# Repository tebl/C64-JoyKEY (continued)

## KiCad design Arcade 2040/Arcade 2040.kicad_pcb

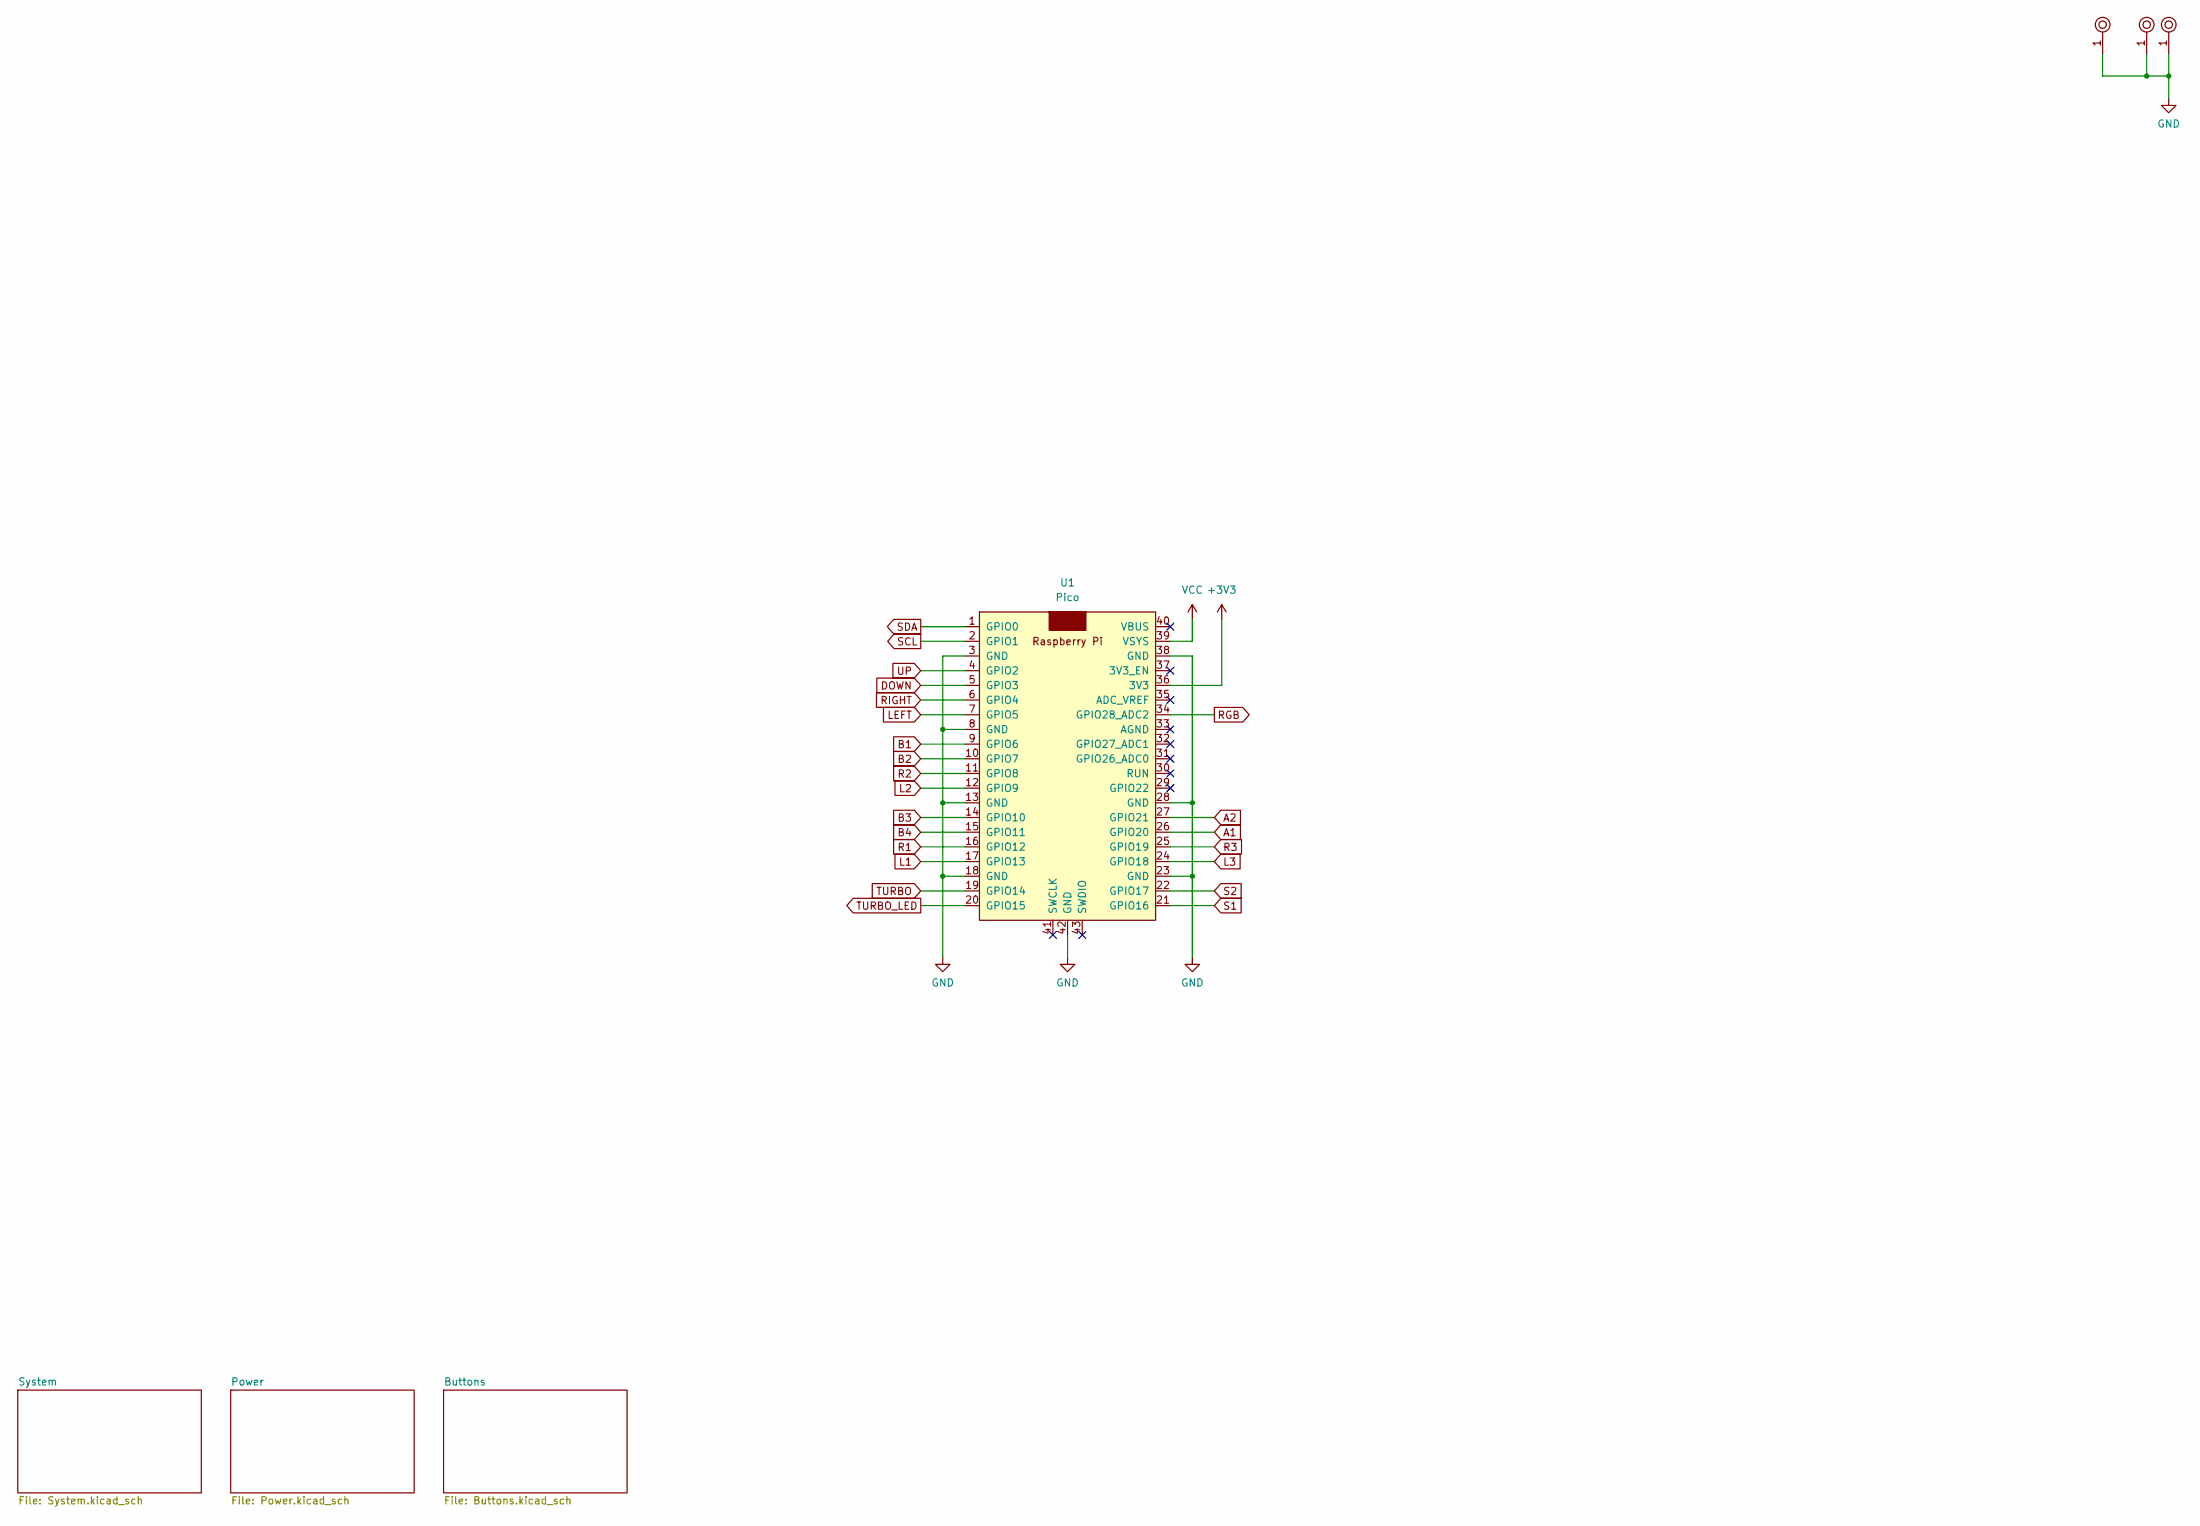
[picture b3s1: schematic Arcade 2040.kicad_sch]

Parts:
M1, M3, M4: Mounting; M3_pin
U1: Pico; RPi_Pico_SMD_TH_Clean

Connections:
+3V3: U1.36 (3V3); also elsewhere on the board
A1: U1.26 (GPIO20); also elsewhere on the board
A2: U1.27 (GPIO21); also elsewhere on the board
B1: U1.9 (GPIO6); also elsewhere on the board
B2: U1.10 (GPIO7); also elsewhere on the board
B3: U1.14 (GPIO10); also elsewhere on the board
B4: U1.15 (GPIO11); also elsewhere on the board
DOWN: U1.5 (GPIO3); also elsewhere on the board
GND: M1.1, M3.1, M4.1, U1.3 (GND), U1.8 (GND), U1.13 (GND), U1.18 (GND), U1.23 (GND), U1.28 (GND), U1.38 (GND), U1.42 (GND); also elsewhere on the board
L1: U1.17 (GPIO13); also elsewhere on the board
L2: U1.12 (GPIO9); also elsewhere on the board
L3: U1.24 (GPIO18); also elsewhere on the board
LEFT: U1.7 (GPIO5); also elsewhere on the board
R1: U1.16 (GPIO12); also elsewhere on the board
R2: U1.11 (GPIO8); also elsewhere on the board
R3: U1.25 (GPIO19); also elsewhere on the board
RGB: U1.34 (GPIO28_ADC2); also elsewhere on the board
RIGHT: U1.6 (GPIO4); also elsewhere on the board
S1: U1.21 (GPIO16); also elsewhere on the board
S2: U1.22 (GPIO17); also elsewhere on the board
SCL: U1.2 (GPIO1); also elsewhere on the board
SDA: U1.1 (GPIO0); also elsewhere on the board
TURBO: U1.19 (GPIO14); also elsewhere on the board
TURBO_LED: U1.20 (GPIO15); also elsewhere on the board
UP: U1.4 (GPIO2); also elsewhere on the board
VCC: U1.39 (VSYS); also elsewhere on the board

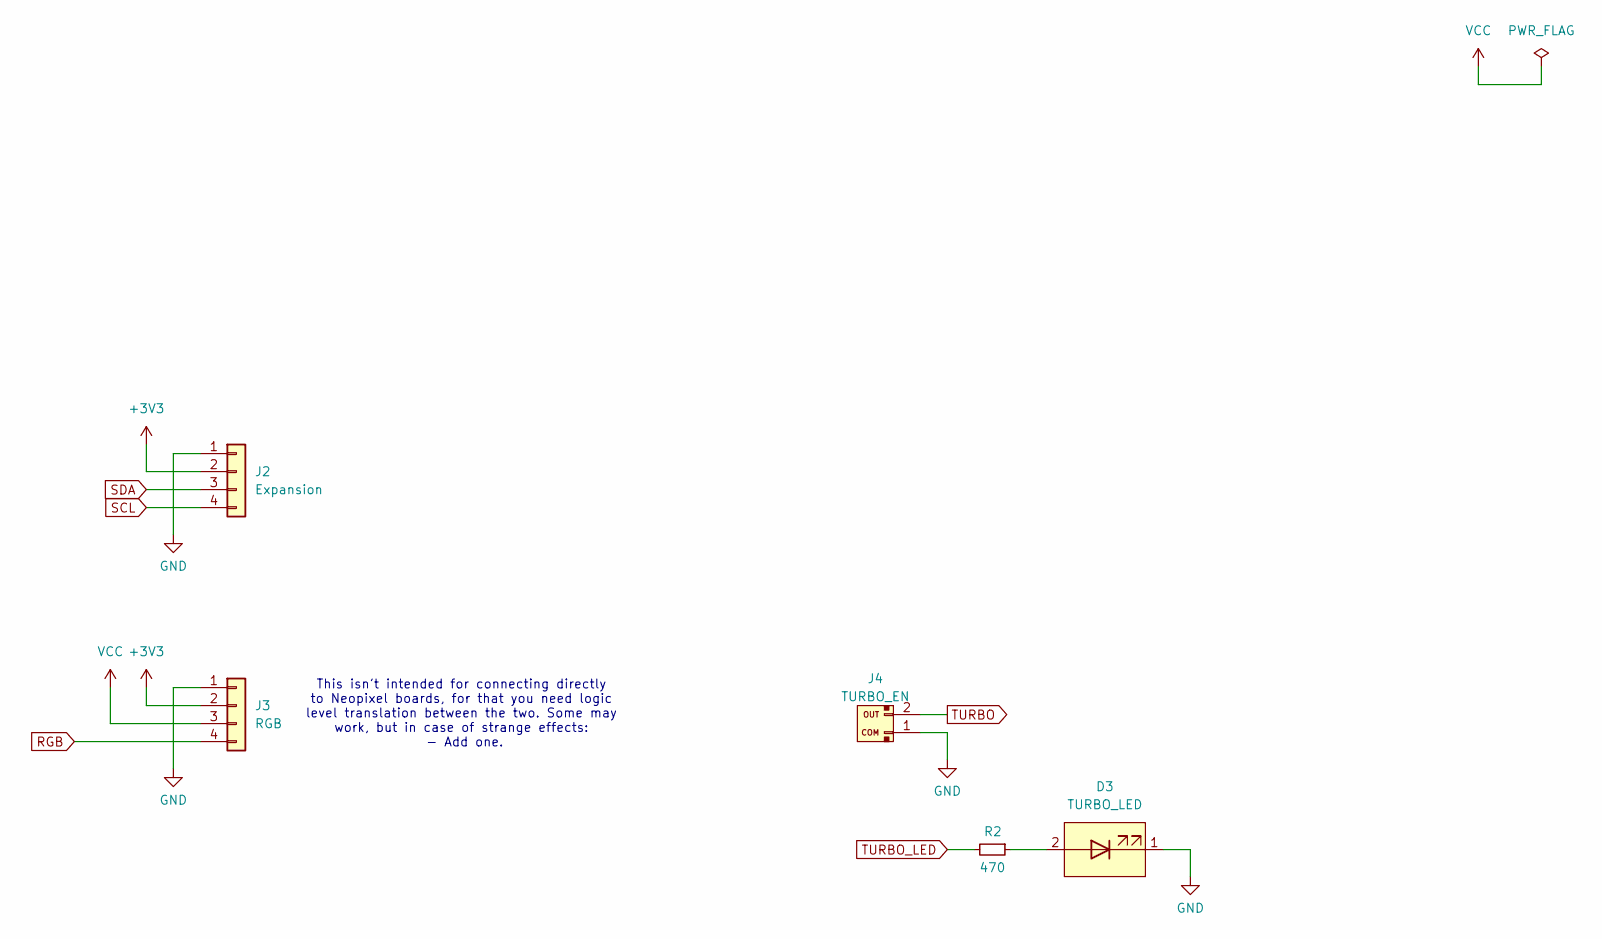
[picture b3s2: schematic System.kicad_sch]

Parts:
D3: TURBO_LED; JST_XH_B2B-XH-A_1x02_P2.50mm_Vertical
J2: Expansion; JST_XH_B4B-XH-A_1x04_P2.50mm_Vertical
J3: RGB; JST_XH_B4B-XH-A_1x04_P2.50mm_Vertical
J4: TURBO_EN; JST_XH_B2B-XH-A_1x02_P2.50mm_Vertical
R2: 470; R_Axial_DIN0207_L6.3mm_D2.5mm_P10.16mm_Horizontal

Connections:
+3V3: J2.2, J3.2; also elsewhere on the board
GND: D3.1 (K), J2.1, J3.1, J4.1; also elsewhere on the board
unnamed: D3.2 (A), R2.1
RGB: J3.4; also elsewhere on the board
SCL: J2.4; also elsewhere on the board
SDA: J2.3; also elsewhere on the board
TURBO: J4.2; also elsewhere on the board
TURBO_LED: R2.2; also elsewhere on the board
VCC: J3.3; also elsewhere on the board

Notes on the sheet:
This isn't intended for connecting directly to Neopixel boards, for that you need logic level translation between the two. Some may work, but in case of strange effects: - Add one.

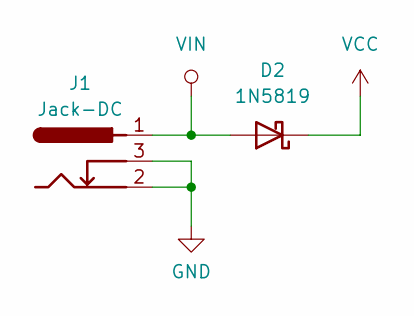
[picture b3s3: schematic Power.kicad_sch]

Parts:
D2: 1N5819; D_DO-41_SOD81_P10.16mm_Horizontal
J1: Jack-DC; BARREL_JACK

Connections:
GND: J1.2, J1.3; also elsewhere on the board
VCC: D2.1 (K); also elsewhere on the board
VIN: D2.2 (A), J1.1

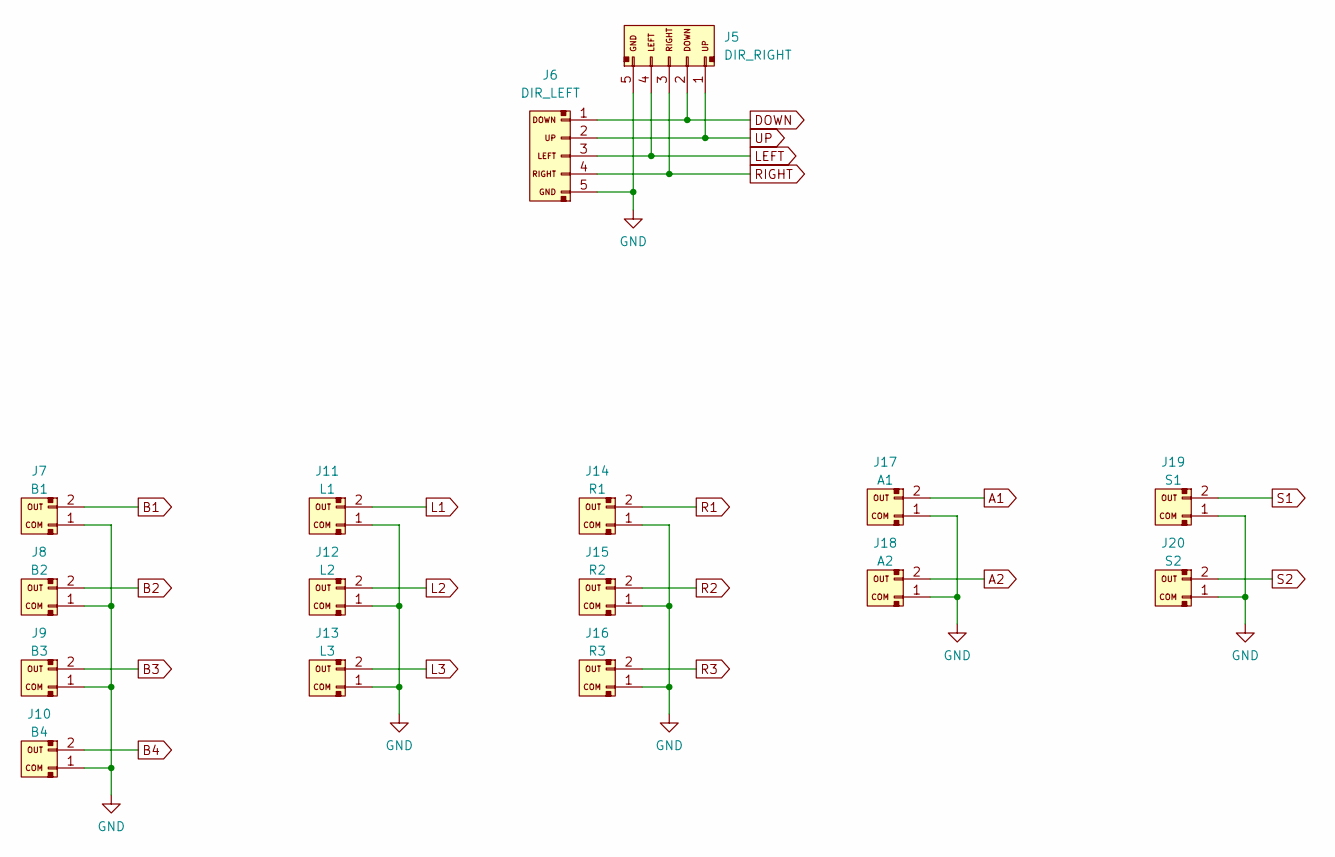
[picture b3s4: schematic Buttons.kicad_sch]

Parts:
J5: DIR_RIGHT; JST_XH_B5B-XH-A_1x05_P2.50mm_Vertical
J6: DIR_LEFT; JST_XH_B5B-XH-A_1x05_P2.50mm_Vertical
J7: B1; JST_XH_B2B-XH-A_1x02_P2.50mm_Vertical
J8: B2; JST_XH_B2B-XH-A_1x02_P2.50mm_Vertical
J9: B3; JST_XH_B2B-XH-A_1x02_P2.50mm_Vertical
J10: B4; JST_XH_B2B-XH-A_1x02_P2.50mm_Vertical
J11: L1; JST_XH_B2B-XH-A_1x02_P2.50mm_Vertical
J12: L2; JST_XH_B2B-XH-A_1x02_P2.50mm_Vertical
J13: L3; JST_XH_B2B-XH-A_1x02_P2.50mm_Vertical
J14: R1; JST_XH_B2B-XH-A_1x02_P2.50mm_Vertical
J15: R2; JST_XH_B2B-XH-A_1x02_P2.50mm_Vertical
J16: R3; JST_XH_B2B-XH-A_1x02_P2.50mm_Vertical
J17: A1; JST_XH_B2B-XH-A_1x02_P2.50mm_Vertical
J18: A2; JST_XH_B2B-XH-A_1x02_P2.50mm_Vertical
J19: S1; JST_XH_B2B-XH-A_1x02_P2.50mm_Vertical
J20: S2; JST_XH_B2B-XH-A_1x02_P2.50mm_Vertical

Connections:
A1: J17.2; also elsewhere on the board
A2: J18.2; also elsewhere on the board
B1: J7.2; also elsewhere on the board
B2: J8.2; also elsewhere on the board
B3: J9.2; also elsewhere on the board
B4: J10.2; also elsewhere on the board
DOWN: J5.2, J6.1; also elsewhere on the board
GND: J5.5, J6.5, J7.1, J8.1, J9.1, J10.1, J11.1, J12.1, J13.1, J14.1, J15.1, J16.1, J17.1, J18.1, J19.1, J20.1; also elsewhere on the board
L1: J11.2; also elsewhere on the board
L2: J12.2; also elsewhere on the board
L3: J13.2; also elsewhere on the board
LEFT: J5.4, J6.3; also elsewhere on the board
R1: J14.2; also elsewhere on the board
R2: J15.2; also elsewhere on the board
R3: J16.2; also elsewhere on the board
RIGHT: J5.3, J6.4; also elsewhere on the board
S1: J19.2; also elsewhere on the board
S2: J20.2; also elsewhere on the board
UP: J5.1, J6.2; also elsewhere on the board

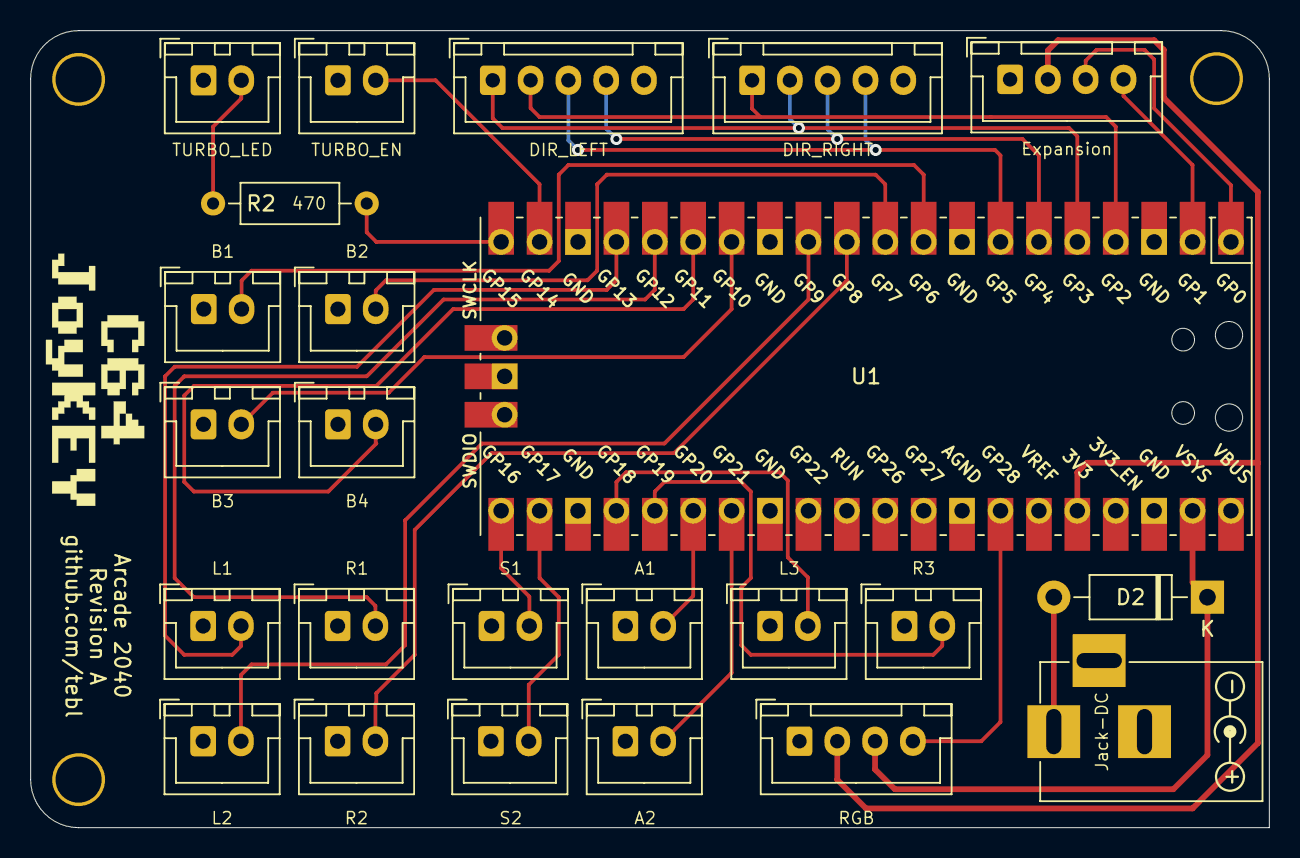
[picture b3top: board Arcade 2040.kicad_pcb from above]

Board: 2 copper layers, 81.9 x 52.7 mm, 27 parts (0 on the bottom side), 28 nets.

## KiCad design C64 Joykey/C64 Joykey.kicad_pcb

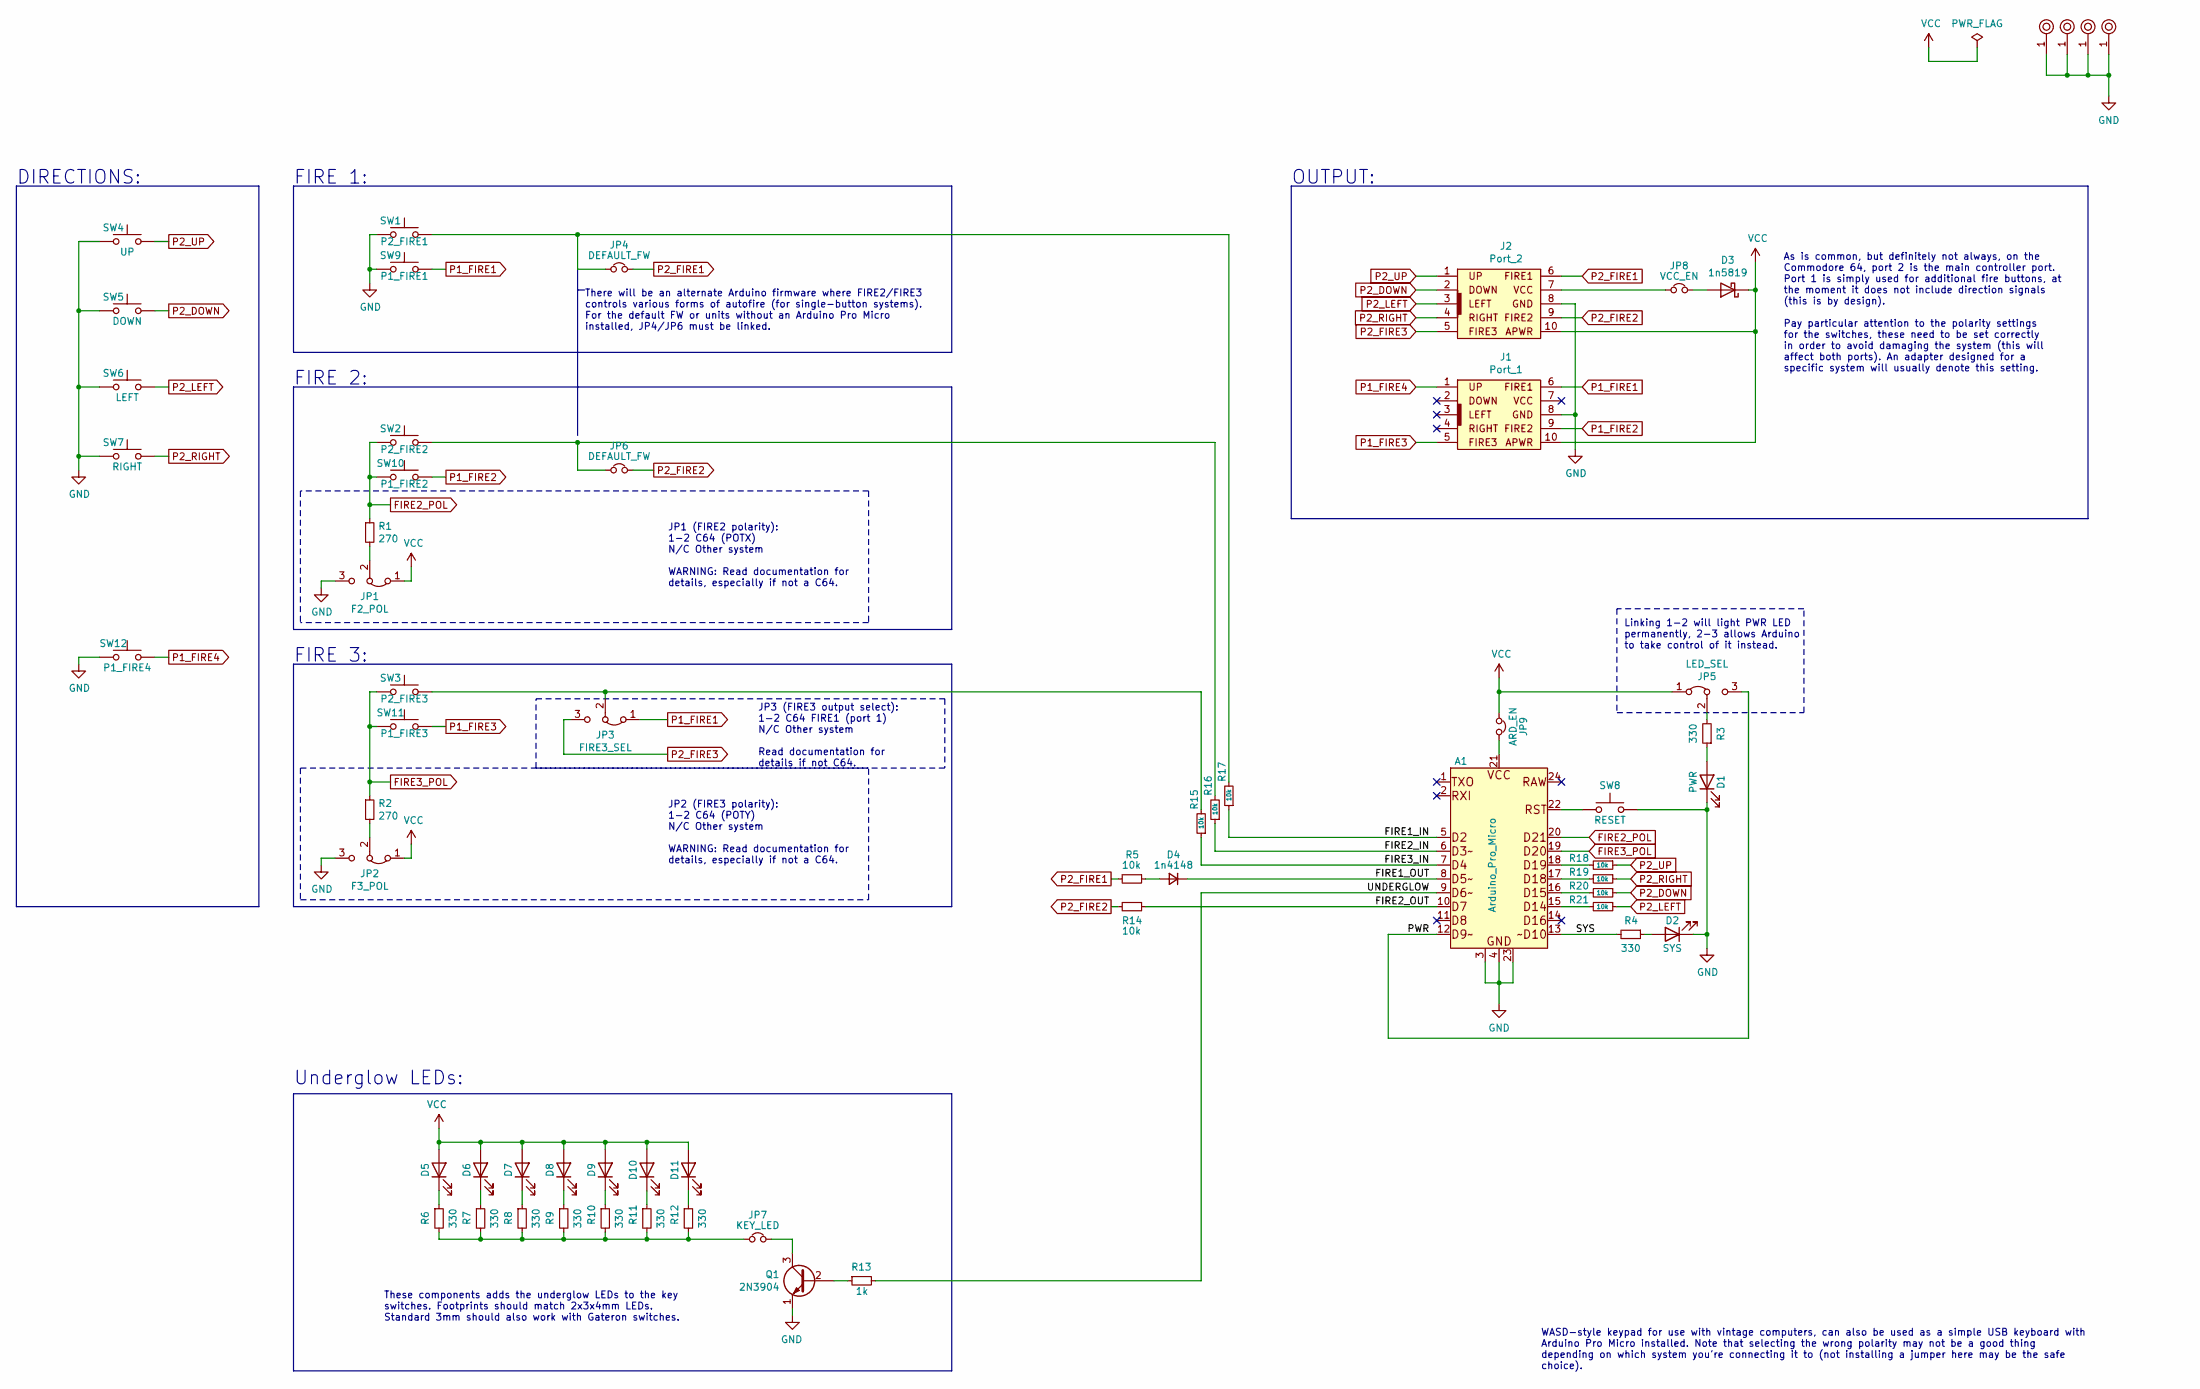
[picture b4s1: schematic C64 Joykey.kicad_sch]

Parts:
A1: Arduino_Pro_Micro
D1: PWR; LED_D5.0mm
D2: SYS; LED_D5.0mm
D3: 1n5819; D_DO-41_SOD81_P10.16mm_Horizontal
D4: 1n4148; D_DO-35_SOD27_P7.62mm_Horizontal
D5, D6, D7, D8, D9, D10, D11: LED; LED_Rectangular_W3.0mm_H2.0mm
J1: Port_1; IDC_Joystick
J2: Port_2; IDC_Joystick
JP1: F2_POL; PinHeader_1x03_P2.54mm_Horizontal
JP2: F3_POL; PinHeader_1x03_P2.54mm_Horizontal
JP3: FIRE3_SEL; PinHeader_1x03_P2.54mm_Horizontal
JP4: DEFAULT_FW; bridge
JP5: LED_SEL; select
JP6: DEFAULT_FW; bridge_r
JP7: KEY_LED; PinHeader_1x02_P2.54mm_Horizontal
JP8: VCC_EN; PinHeader_1x02_P2.54mm_Vertical
JP9: ARD_EN; PinHeader_1x02_P2.54mm_Vertical
M1, M2, M3, M4: Mounting; M3_pin
Q1: 2N3904; 2N3904_TO-92_Horizontal_FlatSideDown
R1, R2: 270; R_Axial_DIN0207_L6.3mm_D2.5mm_P10.16mm_Horizontal
R3, R4, R6, R7, R8, R9, R10, R11, R12: 330; R_Axial_DIN0207_L6.3mm_D2.5mm_P10.16mm_Horizontal
R5, R14, R15, R16, R17, R18, R19, R20, R21: 10k; R_Axial_DIN0207_L6.3mm_D2.5mm_P10.16mm_Horizontal
R13: 1k; R_Axial_DIN0207_L6.3mm_D2.5mm_P10.16mm_Horizontal
SW1: P2_FIRE1; SW_Cherry_MX_1.00u_PCB
SW2: P2_FIRE2; SW_Cherry_MX_1.00u_PCB
SW3: P2_FIRE3; SW_Cherry_MX_1.00u_PCB
SW4: UP; SW_Cherry_MX_1.00u_PCB
SW5: DOWN; SW_Cherry_MX_1.00u_PCB
SW6: LEFT; SW_Cherry_MX_1.00u_PCB
SW7: RIGHT; SW_Cherry_MX_1.00u_PCB
SW8: RESET; SW_PUSH_6mm
SW9: P1_FIRE1; SW_Tactile_SPST_Angled_PTS645Vx31-2LFS
SW10: P1_FIRE2; SW_Tactile_SPST_Angled_PTS645Vx31-2LFS
SW11: P1_FIRE3; SW_Tactile_SPST_Angled_PTS645Vx31-2LFS
SW12: P1_FIRE4; SW_Tactile_SPST_Angled_PTS645Vx31-2LFS

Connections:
/FIRE1_IN: A1.5 (D2), R17.1
/FIRE1_OUT: A1.8 (D5), D4.1 (K)
/FIRE2_IN: A1.6 (D3), R16.1
/FIRE2_OUT: A1.10 (D7), R14.1
/FIRE3_IN: A1.7 (D4), R15.1
/PWR: A1.12 (D9), JP5.3 (B)
/SYS: A1.13 (D10), R4.2
/UNDERGLOW: A1.9 (D6), R13.2
FIRE2_POL: A1.20 (D21), R1.1, SW2.2, SW10.2
FIRE3_POL: A1.19 (D20), R2.1, SW3.2, SW11.2
GND: A1.3 (GND), A1.4 (GND), A1.23 (GND), D1.1 (K), D2.1 (K), J1.8, J2.8, JP1.3 (B), JP2.3 (B), M1.1, M2.1, M3.1, M4.1, Q1.1 (E), SW1.2, SW4.2, SW5.2, SW6.2, SW7.2, SW8.2, SW9.2, SW12.2
unnamed: A1.15 (D14), R21.2
unnamed: A1.16 (D15), R20.2
unnamed: A1.17 (D18), R19.2
unnamed: A1.18 (D19), R18.2
unnamed: A1.22 (RST), SW8.1
unnamed: A1.21 (VCC), JP9.1
unnamed: D1.2 (A), R3.1
unnamed: D2.2 (A), R4.1
unnamed: D3.2 (A), JP8.2
unnamed: D4.2 (A), R5.1
unnamed: D5.1 (K), R6.1
unnamed: D6.1 (K), R7.1
unnamed: D7.1 (K), R8.1
unnamed: D8.1 (K), R9.1
unnamed: D9.1 (K), R10.1
unnamed: D10.1 (K), R11.1
unnamed: D11.1 (K), R12.1
unnamed: J2.7, JP8.1
unnamed: JP1.2 (C), R1.2
unnamed: JP2.2 (C), R2.2
unnamed: JP3.2 (C), R15.2, SW3.1
unnamed: JP4.1, R17.2, SW1.1
unnamed: JP5.2 (C), R3.2
unnamed: JP6.1, R16.2, SW2.1
unnamed: JP7.1, R6.2, R7.2, R8.2, R9.2, R10.2, R11.2, R12.2
unnamed: Q1.2 (B), R13.1
unnamed: JP7.2, Q1.3 (C)
P1_FIRE1: J1.6, JP3.1 (A), SW9.1
P1_FIRE2: J1.9, SW10.1
P1_FIRE3: J1.5, SW11.1
P1_FIRE4: J1.1, SW12.1
P2_DOWN: J2.2, R20.1, SW5.1
P2_FIRE1: J2.6, JP4.2, R5.2
P2_FIRE2: J2.9, JP6.2, R14.2
P2_FIRE3: J2.5, JP3.3 (B)
P2_LEFT: J2.3, R21.1, SW6.1
P2_RIGHT: J2.4, R19.1, SW7.1
P2_UP: J2.1, R18.1, SW4.1
VCC: D3.1 (K), D5.2 (A), D6.2 (A), D7.2 (A), D8.2 (A), D9.2 (A), D10.2 (A), D11.2 (A), J1.10 (EX_VCC), J2.10 (EX_VCC), JP1.1 (A), JP2.1 (A), JP5.1 (A), JP9.2

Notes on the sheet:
As is common, but definitely not always, on the Commodore 64, port 2 is the main controller port. Port 1 is simply used for additional fire buttons, at the moment it does not include direction signals (this is by design). Pay particular attention to the polarity settings for the switches, these nee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
JP3 (FIRE3 output select): 1-2 C64 FIRE1 (port 1) N/C Other system Read documentation for details if not C64.
JP2 (FIRE3 polarity): 1-2 C64 (POTY) N/C Other system WARNING: Read documentation for details, especially if not a C64.
OUTPUT:
WASD-style keypad for use with vintage computers, can also be used as a simple USB keyboard with Arduino Pro Micro installed. Note that selecting the wrong polarity may not be a good thing depending on which system you're connecting it to (not installing a jumper here may be the safe choice).
Underglow LEDs:
There will be an alternate Arduino firmware where FIRE2/FIRE3 controls various forms of autofire (for single-button systems). For the default FW or units without an Arduino Pro Micro installed, JP4/JP6 must be linked.
DIRECTIONS:
FIRE 2:
JP1 (FIRE2 polarity): 1-2 C64 (POTX) N/C Other system WARNING: Read documentation for details, especially if not a C64.
Linking 1-2 will light PWR LED permanently, 2-3 allows Arduino to take control of it instead.
These components adds the underglow LEDs to the key switches. Footprints should match 2x3x4mm LEDs. Standard 3mm should also work with Gateron switches.
FIRE 3:
FIRE 1:

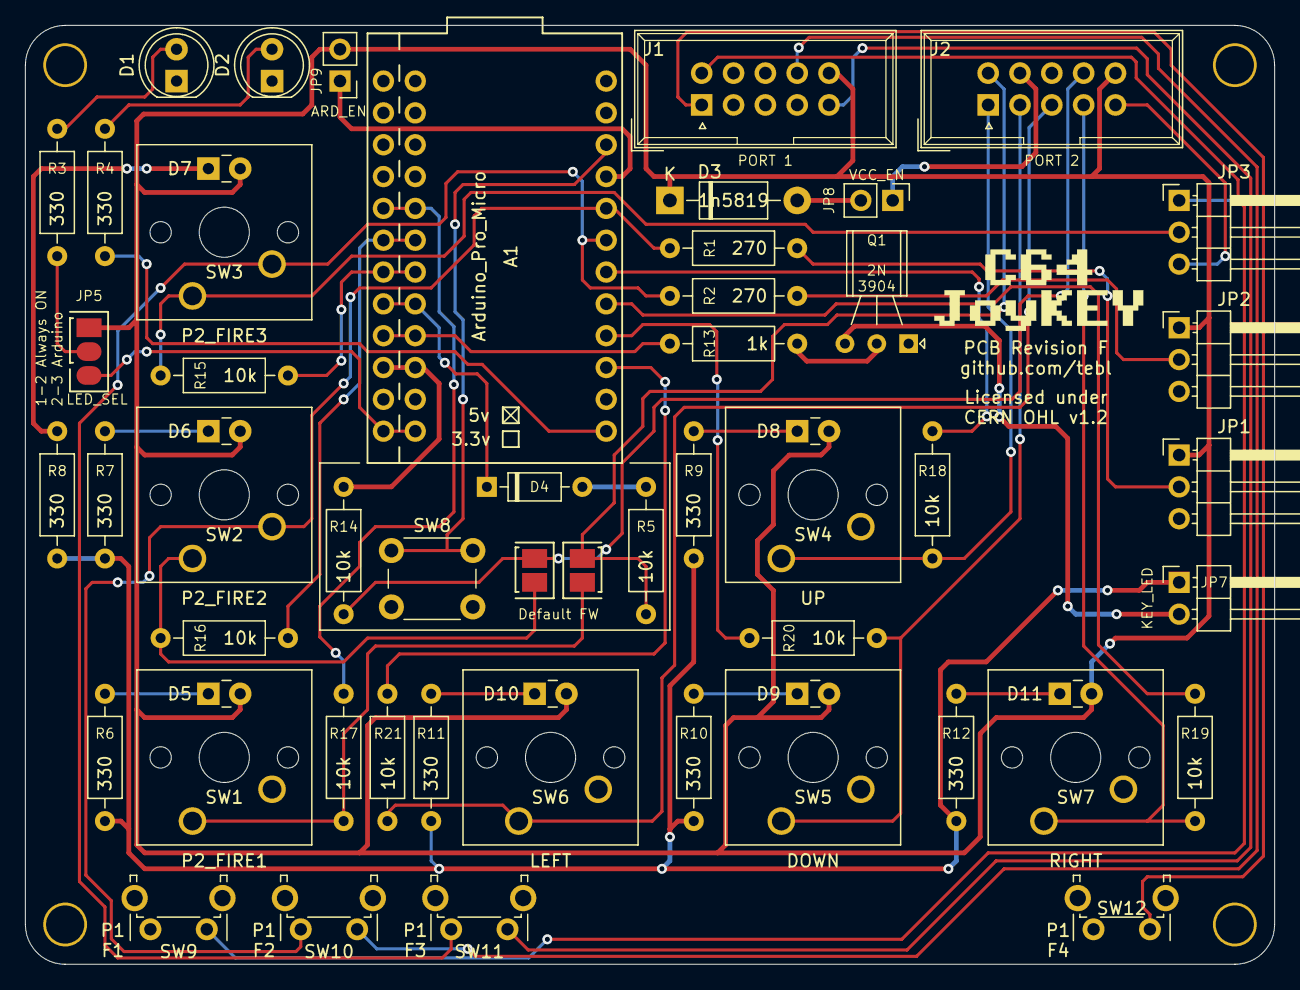
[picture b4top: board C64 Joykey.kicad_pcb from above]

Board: 2 copper layers, 99.7 x 74.9 mm, 61 parts (0 on the bottom side), 50 nets.

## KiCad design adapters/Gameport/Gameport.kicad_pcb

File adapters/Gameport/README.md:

# Gameport

*UNTESTED*

While the IBM PC has seen its fair share of joysticks over time, they were primarily analog though the digital variety have also been regularly seen since the early 1980s as well. The rise of competing gaming consoles soon started to popularize the gamepads over the analog controllers and soon, even the PC saw their share of excellent controllers such as the Gravis Gamepad. While they won't replace the feel and response of an analog flightstick for those type of games, I feel that there are enough variety that the digital controllers also should have their place on the system - for that system I've created a separate Gameport-adapter for the *C64 JoyKEY*. Granted it won't make all that much sense connecting a keyboard-like controller to a computer with a great keyboard, but the ability to use the *C64 JoyKEY Arcade* with it should present as an excellent combination.

The circuit was adapted from the one listed on [asun.net](http://www.asun.net/joystick/joystick.html). Additional information was also listed in a separate [article](https://allpinouts.org/pinouts/connectors/input_device/joystick-pc-gameport/) as well, and could be interesting when working out how the adapter works.

# BOM
The parts listed are the ones I've used when building a MSX adapter for use with the *C64 JoyKEY*, part listed in parenthesis are considered optional (meaning you could build a more limited version of it). 

| Reference     | Item                                      | Count | Order   |
| ------------- | ----------------------------------------- | ----- | ------- |
| PCB           | Fabricate using Gerber files              |    (1)| PCBway
| D1,D2         | 1n4148 small-signal diode (DO-35)         |     2 |
| J1,J2 *1      | 2x5 pin straight header pins or 2x5 IDC   |     2 |
| J3 *2         | 2x8 pin straight header pins or 2x8 IDC   |     1 |
| Q1,Q2 *3      | 2n3906 transistor (TO-92)                 |     2 |
| R5,R6         | 47k ohm resistor                          |     2 |
| R1-R4,R7,R8   | 100k ohm resistor                         |     6 |

1) Breakable dual row pin headers can be used here, but I find it is nicer to have a proper 2x5-pin keyed connector here instead. The cable you will need is a 2x5 pin IDC cable (usually listed as *AVR* or *JTAG* cable), with sufficient length to position where you would like - ideally you will want two of these, but you can make due with one connected to port 1.
2) As with above, 2x8-pin IDC header is recommended. For the cable you will want a 16-pin IDC to a male DB15-ribbon cable - you can buy these ready made from the usual sources. If you can't find one that you like, I recommend picking up 16-pin IDC cables of intended length and then put on a male IDC DB15-connector. While there are special tools created to crimp these on, I find that just pushing hard on them with the handle of a screwdriver works just as well for a single cable.
3) I have not tested this, but I suspect that replacing these with 2n3906 installed backwards may work just as well.

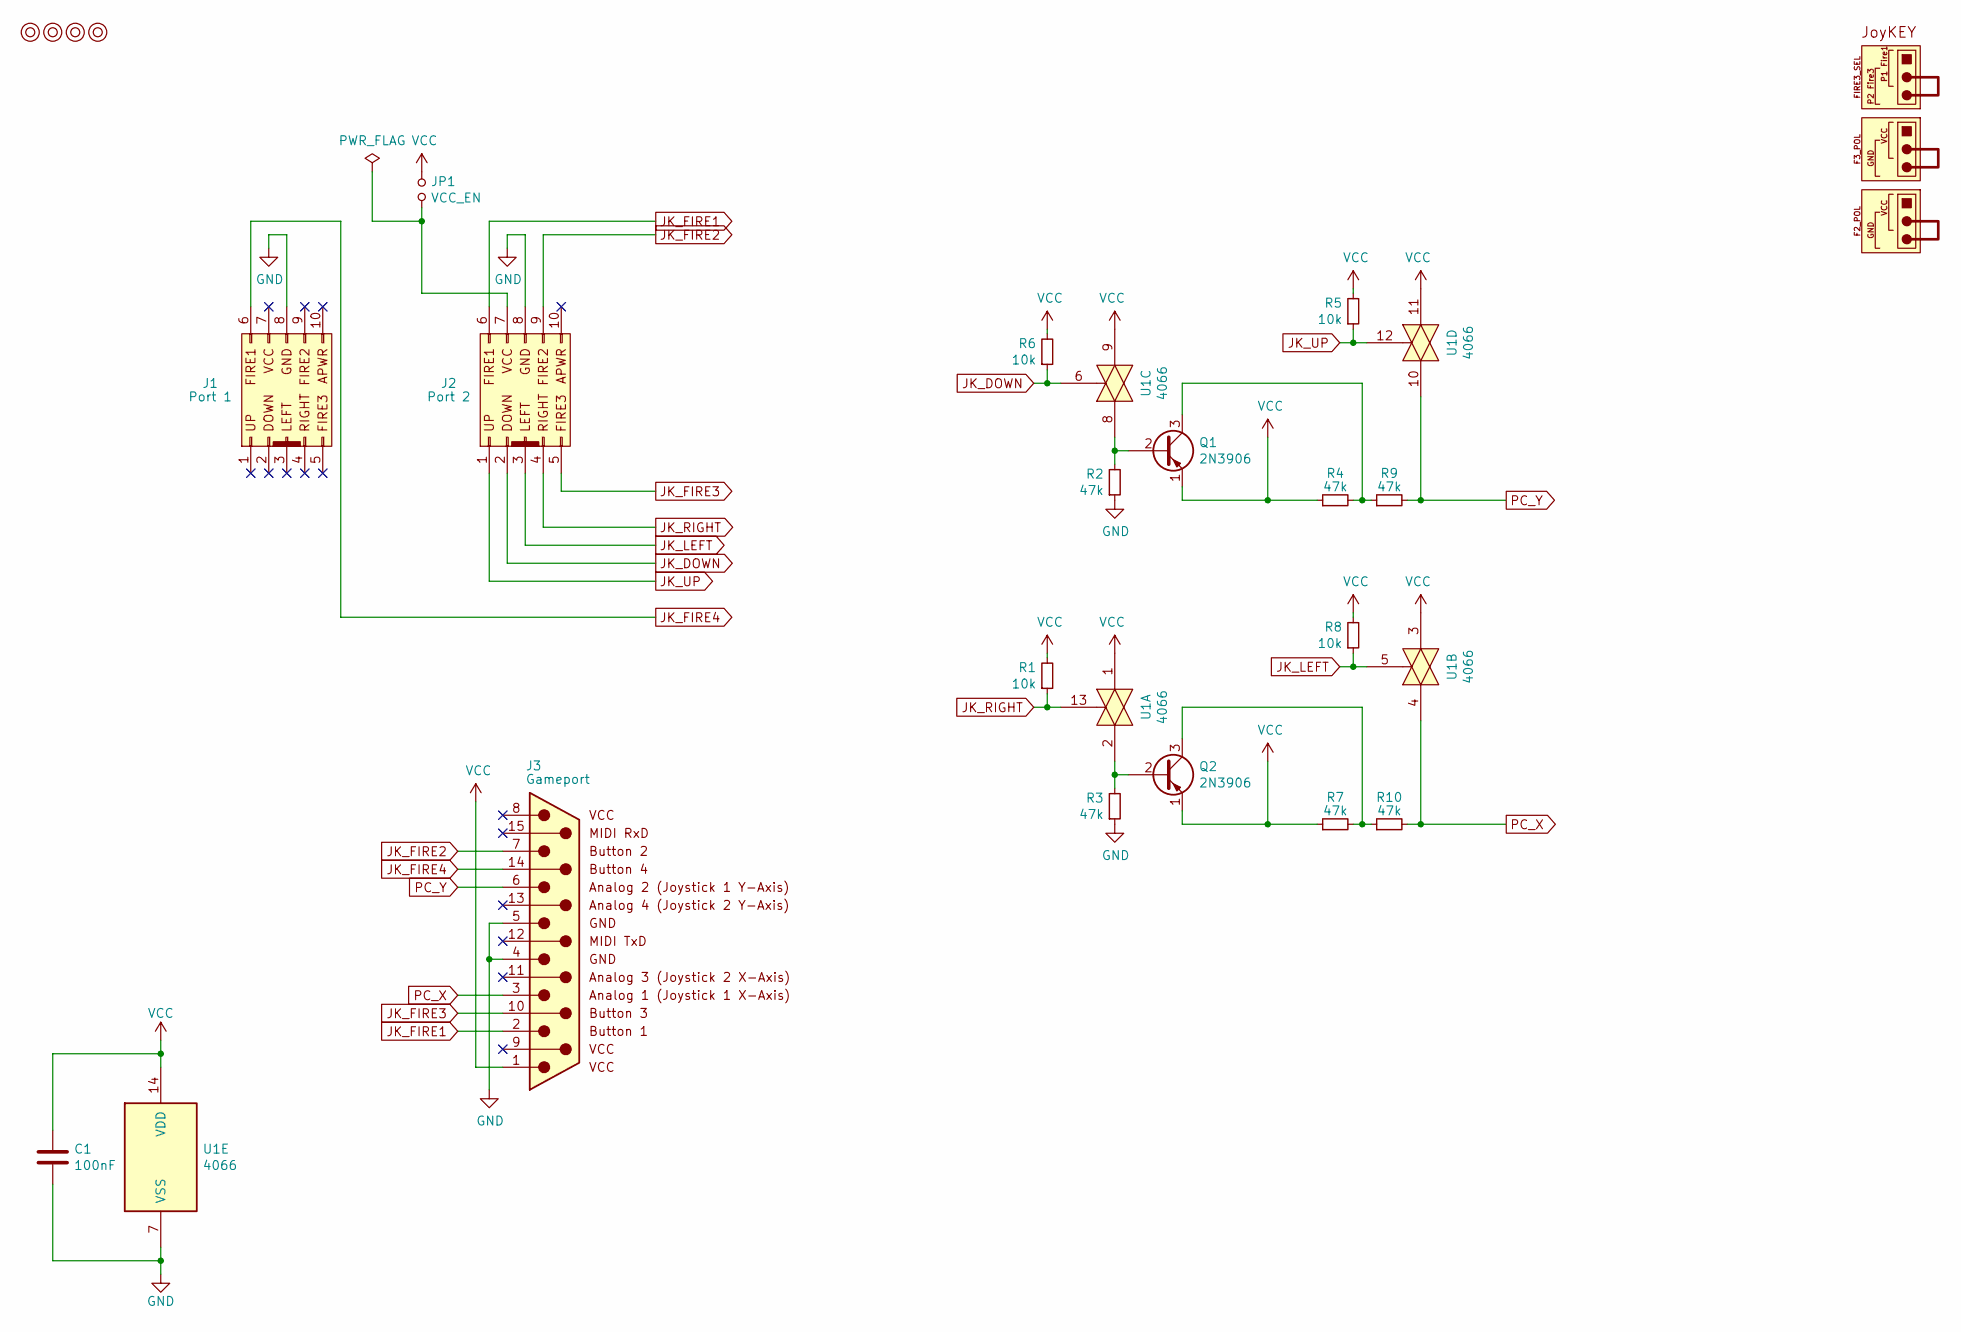
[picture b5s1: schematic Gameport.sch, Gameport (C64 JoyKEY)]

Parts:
C1: 100nF; C_Disc_D4.7mm_W2.5mm_P5.00mm
J1: Port 1; IDC_Joystick
J2: Port 2; IDC_Joystick
J3: Gameport; Gameport_IDC
JP1: VCC_EN; PinHeader_1x02_P2.54mm_Vertical
M1, M2, M3, M4: Mounting; M3_pin
Q1, Q2: 2N3906; TO-92_Inline_Wide
R1, R5, R6, R8: 10k; R_Axial_DIN0207_L6.3mm_D2.5mm_P10.16mm_Horizontal
R2, R3, R4, R7, R9, R10: 47k; R_Axial_DIN0207_L6.3mm_D2.5mm_P10.16mm_Horizontal
U1: 4066; DIP-14_W7.62mm_Socket_LongPads

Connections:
GND: C1.2, J1.8, J2.8, J3.4 (GND), J3.5 (GND), R2.1, R3.1, U1.7 (VSS)
JK_DOWN: J2.2, R6.1, U1.6
JK_FIRE1: J2.6, J3.2 (VCC)
JK_FIRE2: J2.9, J3.7 (BTN2)
JK_FIRE3: J2.5, J3.10 (BTN3)
JK_FIRE4: J1.6, J3.14 (BTN4)
JK_LEFT: J2.3, R8.1, U1.5
JK_RIGHT: J2.4, R1.1, U1.13
JK_UP: J2.1, R5.1, U1.12
unnamed: J2.7, JP1.2
unnamed: Q1.2 (B), R2.2, U1.8
unnamed: Q1.3 (C), R4.2, R9.1
unnamed: Q2.2 (B), R3.2, U1.2
unnamed: Q2.3 (C), R7.2, R10.1
PC_X: J3.3 (A1), R10.2, U1.4
PC_Y: J3.6 (A2), R9.2, U1.10
VCC: C1.1, J3.1 (VCC), JP1.1, Q1.1 (E), Q2.1 (E), R1.2, R4.1, R5.2, R6.2, R7.1, R8.2, U1.1, U1.3, U1.9, U1.11, U1.14 (VDD)

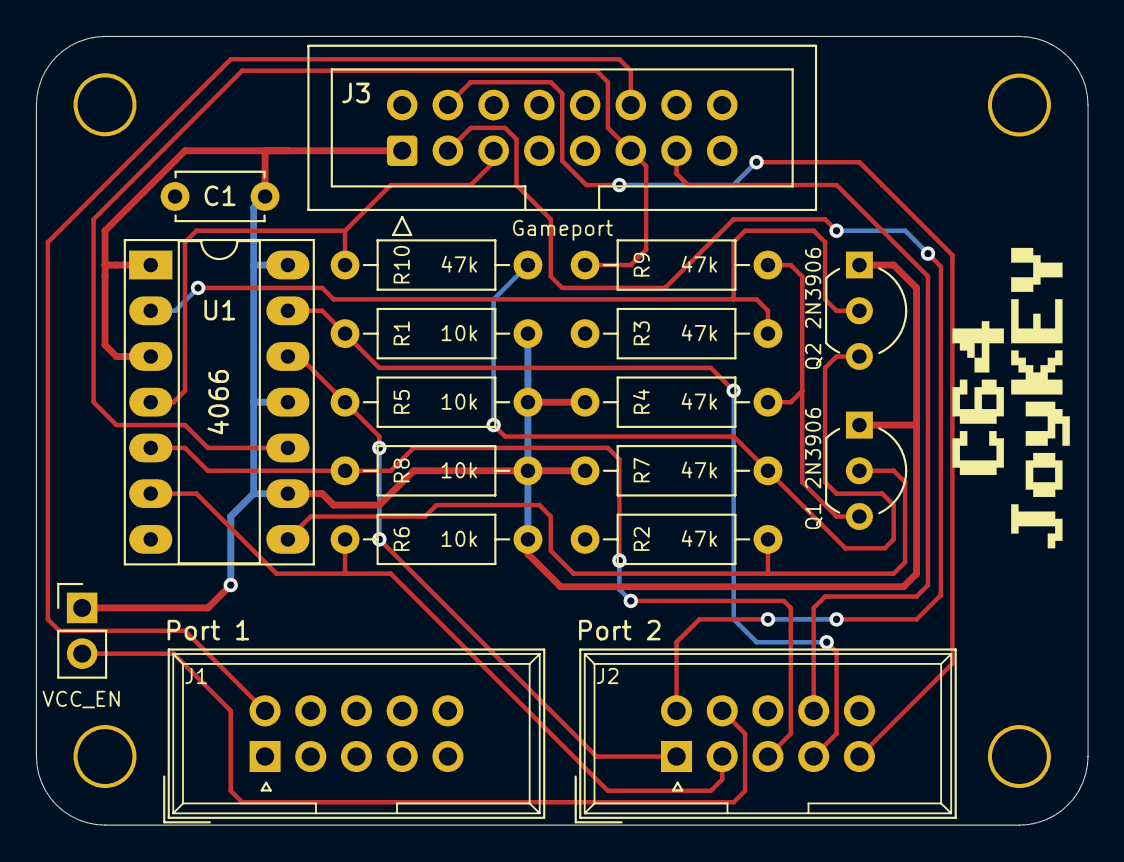
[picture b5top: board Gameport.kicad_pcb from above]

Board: 2 copper layers, 58.4 x 43.8 mm, 22 parts (0 on the bottom side), 17 nets.
